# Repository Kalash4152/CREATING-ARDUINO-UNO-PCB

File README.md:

Arduino Uno PCB Design on KiCad

After long hours of designing, troubleshooting, and refining, I successfully created a custom Arduino Uno PCB using KiCad. This project was a deep dive into schematic design, layout optimization, and overcoming countless DRC (Design Rule Check) errors, routing challenges, and component placement refinements.

I followed the "PCB Design with KiCad" course by Robert Feranec on Udemy, which provided invaluable guidance on best practices, PCB manufacturing constraints, and design optimization. Throughout the process, I learned about:

✅ Microcontroller Integration – Implementing the ATmega328P with proper power and signal routing.
✅ USB-to-Serial Communication – Designing the interface for seamless programming.
✅ Voltage Regulation – Ensuring stable operation with onboard regulators.
✅ Error Debugging – Identifying and fixing schematic and PCB errors through multiple iterations.

This project pushed me to refine my PCB design skills, troubleshoot issues efficiently, and gain a deeper understanding of hardware development.

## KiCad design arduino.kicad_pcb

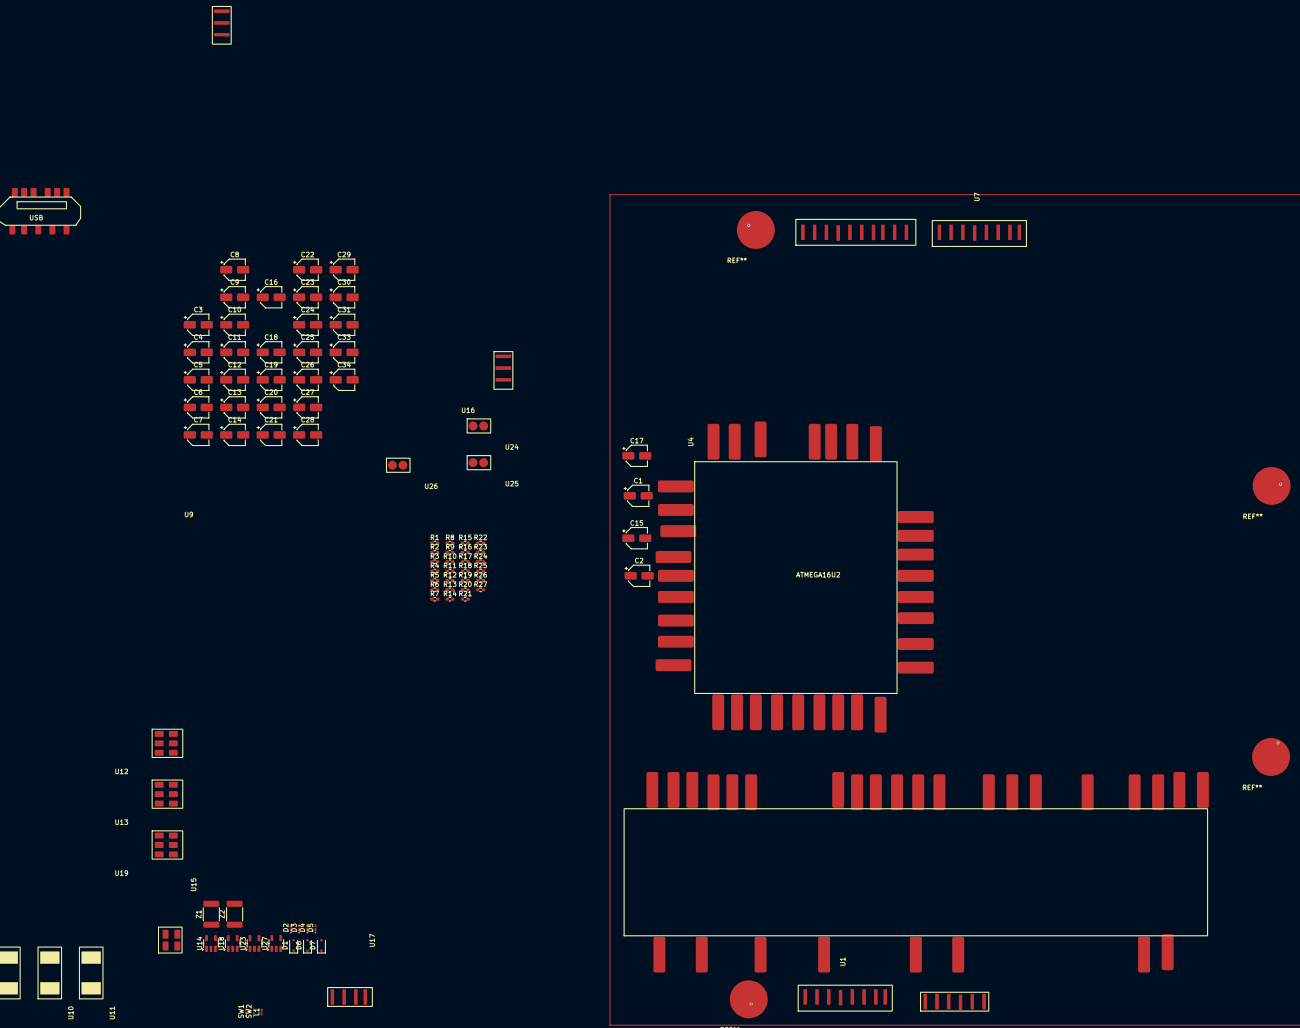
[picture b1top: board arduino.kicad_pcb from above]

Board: 2 copper layers, 98 parts (0 on the bottom side), 68 nets, no tracks yet.

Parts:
C1, C3, C4, C15, C19, C20, C21, C24: 10uf/16v; CP_Elec_4x3.9
C2, C5, C6, C9, C10, C11, C16, C17, C22, C23, C25, C26, C27, C30, C31, C33, C34: 100n; CP_Elec_4x3.9
C7, C8, C13, C14: 18p; CP_Elec_4x3.9
C12: 100n/16v; CP_Elec_4x3.9
C18: 1u; CP_Elec_4x3.9
C28, C29: 100u; CP_Elec_4x3.9
D1, D6, D7: BAT54J; D_SOD-323F
D2, D3: ORANGE LED; LED_0201_0603Metric_Pad0.64x0.40mm_HandSolder
D4, D5: GREEN LED; LED_0201_0603Metric_Pad0.64x0.40mm_HandSolder
L1: 2A/2.2uH; L_0201_0603Metric_Pad0.64x0.40mm_HandSolder
R1, R4, R6, R7, R9, R11, R24, R26: 10k; R_0402_1005Metric_Pad0.72x0.64mm_HandSolder
R2, R3: 1M; R_0402_1005Metric_Pad0.72x0.64mm_HandSolder
R5: 22ohm; R_0402_1005Metric_Pad0.72x0.64mm_HandSolder
R8, R10, R25: 22r; R_0402_1005Metric_Pad0.72x0.64mm_HandSolder
R12: 1k; R_0402_1005Metric_Pad0.72x0.64mm_HandSolder
R13, R14, R15, R16, R17: 550R; R_0402_1005Metric_Pad0.72x0.64mm_HandSolder
R18, R19, R21: OR; R_0402_1005Metric_Pad0.72x0.64mm_HandSolder
R20: 100k; R_0402_1005Metric_Pad0.72x0.64mm_HandSolder
R22, R23: 22R; R_0402_1005Metric_Pad0.72x0.64mm_HandSolder
R27: 560R; R_0402_1005Metric_Pad0.72x0.64mm_HandSolder
SW1, SW2: SW_Push_Dual_x2; D_01005_0402Metric_Pad0.57x0.30mm_HandSolder
U1, U7: 8 pin header
U2: ATMEGA32
U3: 6 pin header
U4: 10pinheader
U5, U6, U8, U10, U11: crystal
U9: ATMEGA16U2
U12, U13, U19: 6PINHEADER
U14, U18, U23, U27: SN74LVC1G00DBV; SOT-23-5
U15: 2_2PINHEADER
U16, U20: 3PINHEADER
U17: 4 pine header
U21: MICRRO USB
U24, U25, U26: POWER PADS
Z1, Z2: CG063; R_1812_4532Metric_Pad1.30x3.40mm_HandSolder

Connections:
3V3: R19.2, U20.3 (x)
+5V: C9.1, C17.1, R15.1, R16.1, R18.1, U7.5 (x), U9.31 (UVCC), U20.1 (x)
+5V/3V3: C21.1, C23.1, C25.1, C26.1, C27.1, C30.1, C33.1, D1.1 (K), D6.1 (K), D7.1 (K), R1.2, R9.1, R11.1, R17.2, R24.1, R26.1, U13.4 (1), U14.5 (VCC), U18.5 (VCC), U19.1 (SHDN), U19.2 (IN), U19.4 (OUT), U19.5 (SENSE), U23.5 (VCC), U27.5 (VCC)
+5V/3v3: C10.1, C11.1, C12.1, C19.1, C29.1, L1.2, R4.1, R18.2, R19.1, R20.1, U7.2 (x), U7.4 (x), U12.5 (1), U20.2 (x)
+AREF: C6.1, C20.1, U2.21 (AREF), U4.8 (x)
/5V USB: C28.1, L1.1, U21.5
/106: U1.7 (x), U2.12 (AIN0)
/ CON USB N: R22.1, U9.29 (D+)
/+3V3: C18.1, U9.27 (UCAP)
/AD0: U2.23 (PCINT8), U3.1 (x)
/AD1: U2.24 (PCINT9), U3.2 (x)
/AD2: U2.25 (PCINT10), U3.3 (x)
/AD3: U2.26 (PCINT11), U3.4 (x)
/AUTORESET: C24.1, R11.2, U14.1
/BUTTON RESET: D1.2 (A), R9.2, R10.1, SW1.2 (D)
/CLK: R5.1, U2.19 (PCINT5)
/CON USB P: R23.1, U9.30 (D-)
/I00: R6.1, U1.1 (x), U2.2 (RXD(PCINT15))
/I01: R7.1, U1.2 (x), U2.3 (TXD(PCINT16))
/IO2: U1.3 (x), U2.4 (INT0(PCINT17))
/IO3: U1.4 (x), U2.5 (INT1(PCINT18))
/IO4: U1.5 (x), U2.6 (TO(PCINT19))
/IO5: U1.6 (x), U2.11 (T1)
/IO7: U1.8 (x), U2.13 (AIN1)
/IO8: U2.14 (ICP1), U4.1 (x)
/IO9: U2.15 (PCINT1), U4.2 (x)
/MISO: U2.18 (PCINT4), U4.5 (x), U12.1
/RX LED: D2.1 (K), U9.18 (PD4)
/RXD: R7.2, U9.16 (PD2)
/SCK: U18.1, U18.2
/SCL: U2.28 (PCINT13), U3.6 (x), U4.10 (x)
/SDA: U2.27 (PCINT12), U3.5 (x), U4.9 (x)
/SS: U2.16 (PCINT2), U4.3 (x)
/TX LED: D3.1 (K), U9.19 (PD5)
/TXD: R6.2, U9.17 (PD3)
/USER BUTTON: D6.2 (A), R24.2, R25.1, SW2.2 (D)
/USER BUTTON BUF: C31.1, R25.2, U23.1, U23.2
GND: C1.2, C2.2, C3.2, C4.2, C5.2, C6.2, C7.1, C8.1, C9.2, C10.2, C11.2, C12.2, C13.1, C14.1, C15.2, C16.2, C17.2, C18.2, C19.2, C20.2, C21.2, C22.2, C23.2, C25.2, C26.2, C27.2, C28.2, C29.2, C30.2, C31.2, C33.2, C34.2, D4.1 (K), R1.1, R4.2, R12.1, R13.1, R14.1, R20.2, R21.1, R27.2, SW1.1 (C), SW2.1 (C), U2.1 (RESET(PCINT14)), U2.8 (GND), U2.22 (GND), U4.7 (x), U7.3 (x), U7.6 (x), U7.7 (x), U9.3 (GND), U9.21 (PD7), U9.24 (RESET(PC1)), U9.28 (UGND), U12.3 (1), U12.6 (1), U13.6 (1), U14.3 (GND), U14.4, U17.1 (x), U17.4 (x), U18.3 (GND), U19.3 (GND), U19.6 (EPAD), U21.1, U21.8, U21.9, U21.10, U21.11, U23.3 (GND), U27.3 (GND), U27.4, Z1.2, Z2.2
unnamed: C22.1, R10.2, U14.2
unnamed: C24.2, U16.3 (x)
unnamed: D2.2 (A), R13.2
unnamed: D3.2 (A), R14.2
unnamed: D4.2 (A), R15.2, R16.2
unnamed: D5.2 (A), U18.4
unnamed: D5.1 (K), R17.1
unnamed: C34.1, D7.2 (A), R26.2, U27.1, U27.2
unnamed: R5.2, U4.6 (x)
unnamed: R8.2, U13.2 (1)
unnamed: R12.2, U16.1 (x)
unnamed: R21.2, U21.2
unnamed: R22.2, U21.4
unnamed: R23.2, U21.3, Z1.1, Z2.1
unnamed: R27.1, U23.4
unnamed: C4.1, C5.1, U2.20 (AVCC)
unnamed: U2.17 (PCINT3), U4.4 (x), U12.4 (1)
unnamed: C7.2, R2.2, U2.9 (PCINT6)
unnamed: C8.2, R2.1, U2.10 (PCINT7)
unnamed: C2.1, C3.1, U2.7 (VCC)
unnamed: C1.1, C15.1, C16.1, U9.4 (VCC), U9.32 (AVCC)
unnamed: R8.1, U9.7 (PB1(PCINT1))
unnamed: U9.8 (PB2(PCINT2)), U13.5 (1)
unnamed: U9.9 (PB3(PCINT3)), U13.1, U17.3 (x)
unnamed: U9.10 (PB4(PCINT4)), U15.4
unnamed: U9.11 (PB5(PCINT5)), U15.3
unnamed: U9.33 (PB6), U15.2
unnamed: C13.2, R3.2, U9.2 (PC0)
unnamed: C14.2, R3.1, U9.1 (XTAL1)
unnamed: U13.3 (1), U17.2 (x)
